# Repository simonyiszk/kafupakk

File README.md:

# ha5kfu-akksipakk
LiFePO4 kémiájú cellákból épített 12V-os akkumulátor kitelepüléshez és miegymáshoz

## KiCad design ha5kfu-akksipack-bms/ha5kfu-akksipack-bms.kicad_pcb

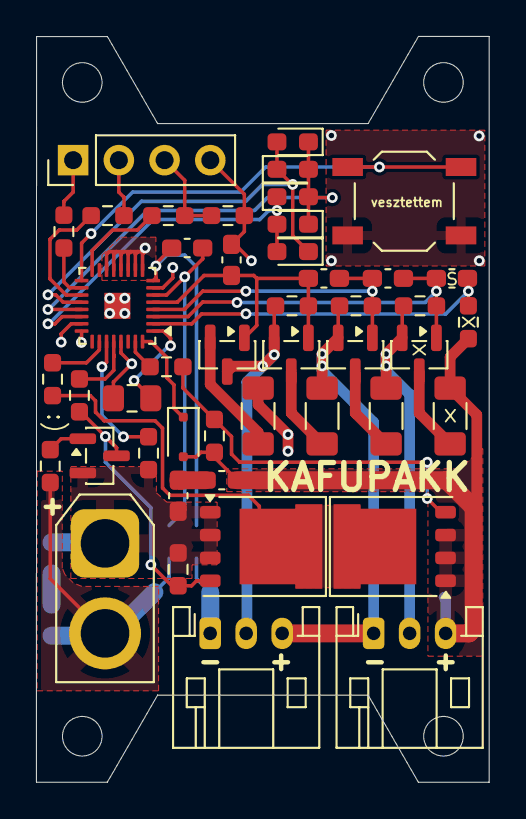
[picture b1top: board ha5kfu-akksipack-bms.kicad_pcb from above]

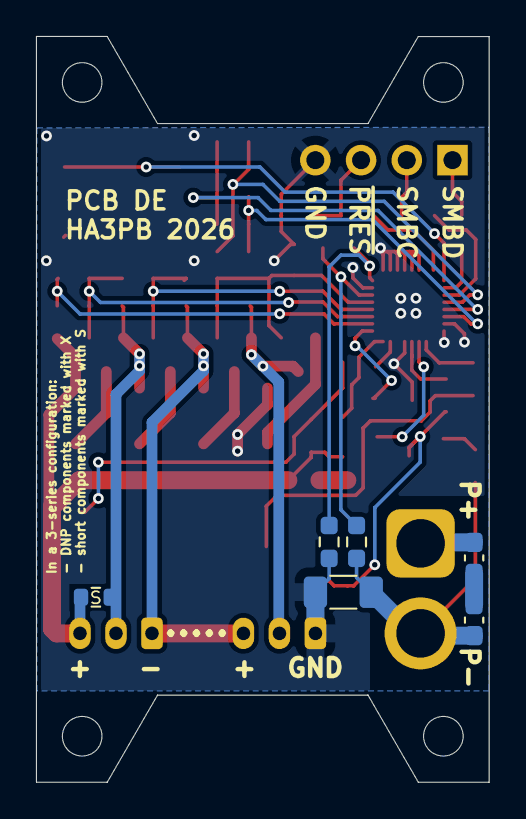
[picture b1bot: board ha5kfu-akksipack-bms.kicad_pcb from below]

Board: 2 copper layers, 25.2 x 41.4 mm, 52 parts (6 on the bottom side), 39 nets.

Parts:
BT1: LiFePO4; R_0603_1608Metric
C1, C2, C3, C4, C5, C6, C7, C8, C10: 100n; C_0603_1608Metric_Pad1.08x0.95mm_HandSolder
C9: 2u2; C_0805_2012Metric_Pad1.18x1.45mm_HandSolder
D1: LED1; LED_0603_1608Metric_Pad1.05x0.95mm_HandSolder
D2: LED2; LED_0603_1608Metric_Pad1.05x0.95mm_HandSolder
D3: LED3; LED_0603_1608Metric_Pad1.05x0.95mm_HandSolder
D4: LED4; LED_0603_1608Metric_Pad1.05x0.95mm_HandSolder
D5: LED5; LED_0603_1608Metric_Pad1.05x0.95mm_HandSolder
D6: BAT54; D_SOD-323F
IC1: BQ4050RSMR; VQFN-32-1EP_4x4mm_P0.4mm_EP2.8x2.8mm
J1: PACK; AMASS_XT30U-F_1x02_P5.0mm_Vertical
J2: PACK1; JST_PH_S3B-PH-K_1x03_P2.00mm_Horizontal
J3: PACK2; JST_PH_S3B-PH-K_1x03_P2.00mm_Horizontal
J4: COM; PinHeader_1x04_P2.54mm_Vertical
Q1, Q2: AON6512; PQFN-8-EP_6x5mm_P1.27mm_Generic
Q3: 2N7002; SOT-23
Q4, Q5, Q6: AO3400A; SOT-23
Q7: AO3401A; SOT-23
R1, R2: 10M; R_0603_1608Metric_Pad0.98x0.95mm_HandSolder
R3, R19: 10k; R_0603_1608Metric_Pad0.98x0.95mm_HandSolder
R4, R8, R12, R17: 200; R_0603_1608Metric_Pad0.98x0.95mm_HandSolder
R5, R9, R15, R20: 33; R_1206_3216Metric_Pad1.30x1.75mm_HandSolder
R6, R7: 5k1; R_0603_1608Metric_Pad0.98x0.95mm_HandSolder
R10, R13, R16, R18, R22, R23: 100; R_0603_1608Metric_Pad0.98x0.95mm_HandSolder
R11: 10k precision; R_0603_1608Metric_Pad0.98x0.95mm_HandSolder
R21: 0.001; R_1206_3216Metric_Pad1.30x1.75mm_HandSolder
SW1: DISP; SW_SPST_TL3342

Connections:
/PACK+: C2.2, C4.1, J1.1, Q2.1 (S), Q2.2 (S), Q2.3 (S), Q3.2 (S), R2.1, R11.1
/PACK-: C6.2, J1.2, R3.2, R21.2, R23.2
/SMB_SCL: J4.2, R13.1
/SMB_SDA: J4.1, R16.2
/~PRES: J4.3, R18.2, R19.2
GND: C8.2, C9.2, IC1.7 (NC_1), IC1.9 (VSS), IC1.10 (TS1), IC1.11 (TS2), IC1.12 (TS3), IC1.13 (TS4), IC1.14 (NC_2), IC1.23 (PTC), IC1.24 (PTCEN), IC1.29 (NC_3), IC1.33 (TP), J3.1, J4.4, R19.1, R20.2, R21.1, R22.2, SW1.2
unnamed: BT1.1 (+), C1.1, D6.2 (A), J2.3, Q1.1 (S), Q1.2 (S), Q1.3 (S), R1.1, R4.1, R5.1
unnamed: BT1.2 (-), J2.2, Q4.2 (S), R8.1, R9.1
unnamed: C1.2, C2.1
unnamed: C4.2, C6.1
unnamed: D1.2 (A), D2.1 (K), D5.1 (K), IC1.20 (LEDCNTLA)
unnamed: D1.1 (K), D2.2 (A), D3.2 (A), D4.1 (K), IC1.21 (LEDCNTLB)
unnamed: D3.1 (K), D4.2 (A), D5.2 (A), IC1.22 (LEDCNTLC)
unnamed: D6.1 (K), IC1.32 (BAT)
unnamed: IC1.31 (CHG), R6.2
unnamed: IC1.28 (DSG), R7.2
unnamed: IC1.27 (PACK), R11.2
unnamed: C9.1, IC1.1 (PBI)
unnamed: IC1.19 (SMBC), R13.2
unnamed: IC1.18 (SMBD), R16.1
unnamed: C10.2, IC1.6 (SRN), R23.1
unnamed: C10.1, IC1.8 (SRP), R22.1
unnamed: C7.2, C8.1, IC1.5 (VC1), Q6.1 (G), Q7.1 (G), R17.2
unnamed: C5.2, C7.1, IC1.4 (VC2), Q5.1 (G), R12.2
unnamed: C3.2, C5.1, IC1.3 (VC3), Q4.1 (G), R8.2
unnamed: C3.1, IC1.2 (VC4), R4.2
unnamed: IC1.26 (VCC), R10.2
unnamed: IC1.17 (~DISP), SW1.1
unnamed: IC1.16 (~PRES/~SHDN), R18.1
unnamed: J2.1, J3.3, Q5.2 (S), R12.1, R15.1
unnamed: J3.2, Q6.2 (S), Q7.3 (D), R17.1
unnamed: Q1.5 (D), Q2.5 (D), R10.1
unnamed: Q1.4 (G), R1.2, R6.1
unnamed: Q2.4 (G), Q3.3 (D), R2.2, R7.1
unnamed: Q3.1 (G), R3.1
unnamed: Q4.3 (D), R5.2
unnamed: Q5.3 (D), R9.2
unnamed: Q6.3 (D), R15.2
unnamed: Q7.2 (S), R20.1

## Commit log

2025-10-11 Add BMS schematic
2025-10-12 Add pull-down for /SHDN
2025-12-23 Add initial PCB design
2025-12-25 Add LEDs, modify PCB
2025-12-26 Complete PCB, add comments (as documentation) to schematic
2026-01-08 Add mounting holes
2026-01-12 Add draft for enclosure
2026-01-12 Add PCB 3D models
